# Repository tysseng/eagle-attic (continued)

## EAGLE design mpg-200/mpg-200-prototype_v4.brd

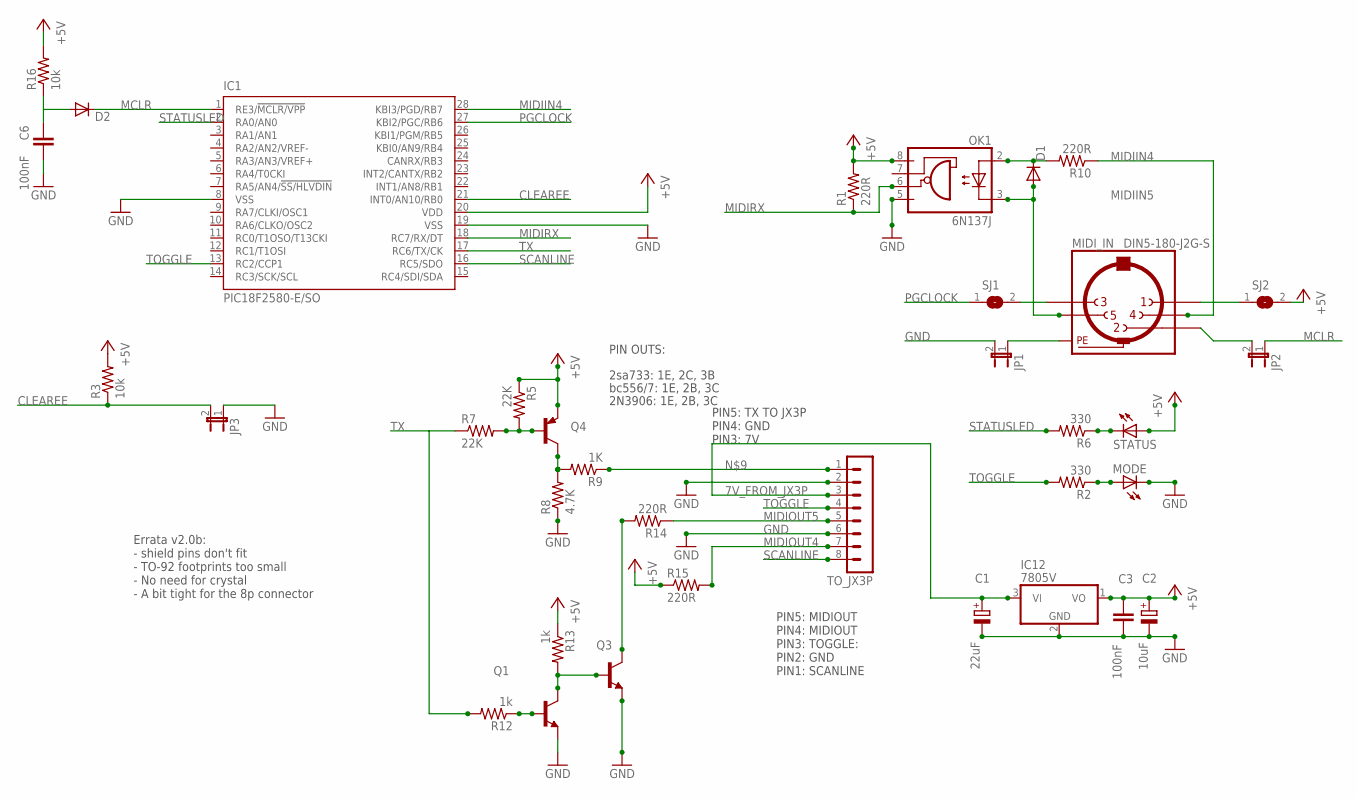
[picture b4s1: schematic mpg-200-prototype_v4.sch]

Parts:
C1: 22uF; E2,5-5
C2: 10uF; E2,5-5
C3, C6: 100nF; C0805
D1, D2: DIODE-SOD80C; SOD80C
IC1: PIC18F2580-E/SO; SO28W
IC12: 7805V; TO92
JP1, JP2, JP3: JP1E; JP1
MIDI_IN: DIN5-180-J2G-S; DIN5-180-J-DUAL-GND-SHORT
MODE: LED3MM
OK1: 6N137J; DIL08-J
Q1, Q3: 2N3904-NPN-TO92-EBC; TO92-EBC
Q4: 2N3906-PNP-TO92-EBC; TO92-EBC
R1, R10, R14, R15: 220R; R0805
R2, R6: 330; R0805
R3, R16: 10k; R0805
R5, R7: 22K; R0805
R8: 4.7K; R0805
R9: 1K; R0805
R12, R13: 1k; R0805
SJ1, SJ2: SJ
STATUS: LED3MM
TO_JX3P: MA08-1

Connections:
7V_FROM_JX3P: C1.+, IC12.3 (VI), TO_JX3P.3
+5V: C2.+, C3.1, IC1.20 (VDD), IC12.1 (VO), OK1.8 (VCC), Q4.E, R1.2, R3.2, R5.1, R13.1, R15.1, R16.2, SJ2.2, STATUS.A
CLEAREE: IC1.21 (INT0/AN10/RB0), JP3.2, R3.1
GND: C1.-, C2.-, C3.2, C6.2, IC1.8 (VSS), IC1.19 (VSS), IC12.2 (GND), JP1.2, JP3.1, MODE.K (C), OK1.5 (GND), Q1.E, Q3.E, R8.1, TO_JX3P.2, TO_JX3P.6
MCLR: D2.C, IC1.1 (RE3/!MCLR/VPP), JP2.1
MIDIIN4: IC1.28 (KBI3/PGD/RB7), MIDI_IN.4, R10.1
MIDIIN5: D1.A, MIDI_IN.5, OK1.3 (C)
MIDIOUT4: R15.2, TO_JX3P.7
MIDIOUT5: R14.1, TO_JX3P.5
MIDIRX: IC1.18 (RC7/RX/DT), OK1.6 (VO), R1.1
unnamed: R6.1, STATUS.K (C)
unnamed: Q4.B, R5.2, R7.2
unnamed: MODE.A, R2.1
unnamed: Q1.B, R12.1
unnamed: D1.C, OK1.2 (A), R10.2
unnamed: Q4.C, R8.2, R9.2
unnamed: Q1.C, Q3.B, R13.2
unnamed: Q3.C, R14.2
unnamed: R9.1, TO_JX3P.1
unnamed: MIDI_IN.3, SJ1.2
unnamed: JP2.2, MIDI_IN.2
unnamed: MIDI_IN.1, SJ2.1
unnamed: JP1.1, MIDI_IN.PE, MIDI_IN.PE@1 (PE), MIDI_IN.PE@2 (PE), MIDI_IN.PE@3 (PE)
unnamed: C6.1, D2.A, R16.1
PGCLOCK: IC1.27 (KBI2/PGC/RB6), SJ1.1
SCANLINE: IC1.16 (RC5/SDO), TO_JX3P.8
STATUSLED: IC1.2 (RA0/AN0), R6.2
TOGGLE: IC1.13 (RC2/CCP1), R2.2, TO_JX3P.4
TX: IC1.17 (RC6/TX/CK), R7.1, R12.2

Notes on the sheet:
2sa733: 1E, 2C, 3B
bc556/7: 1E, 2B, 3C
2N3906: 1E, 2B, 3C
PIN OUTS:
PIN5: MIDIOUT PIN4: MIDIOUT PIN3: TOGGLE: PIN2: GND PIN1: SCANLINE
PIN5: TX TO JX3P PIN4: GND PIN3: 7V
Errata v2.0b: - shield pins don't fit - TO-92 footprints too small - No need for crystal - A bit tight for the 8p connector

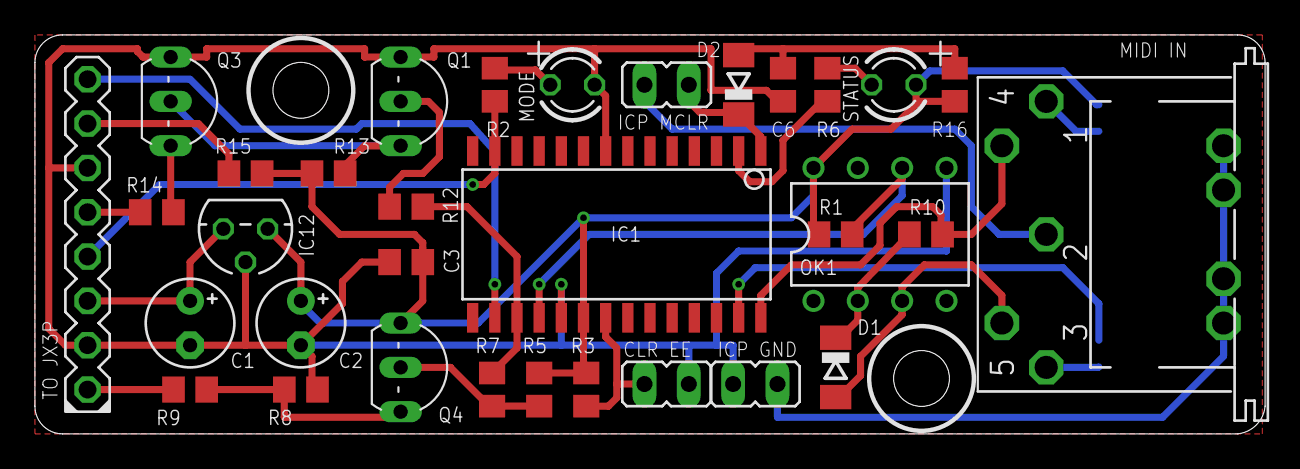
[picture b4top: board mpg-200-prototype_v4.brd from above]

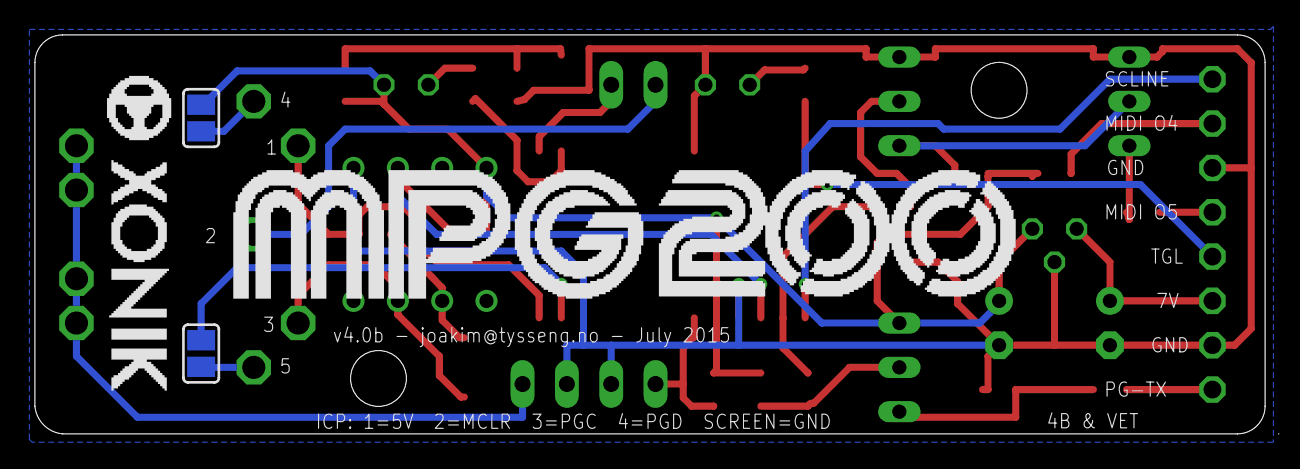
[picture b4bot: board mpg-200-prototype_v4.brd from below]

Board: 2 copper layers, 70.5 x 22.9 mm, 35 parts (2 on the bottom side), 29 nets.

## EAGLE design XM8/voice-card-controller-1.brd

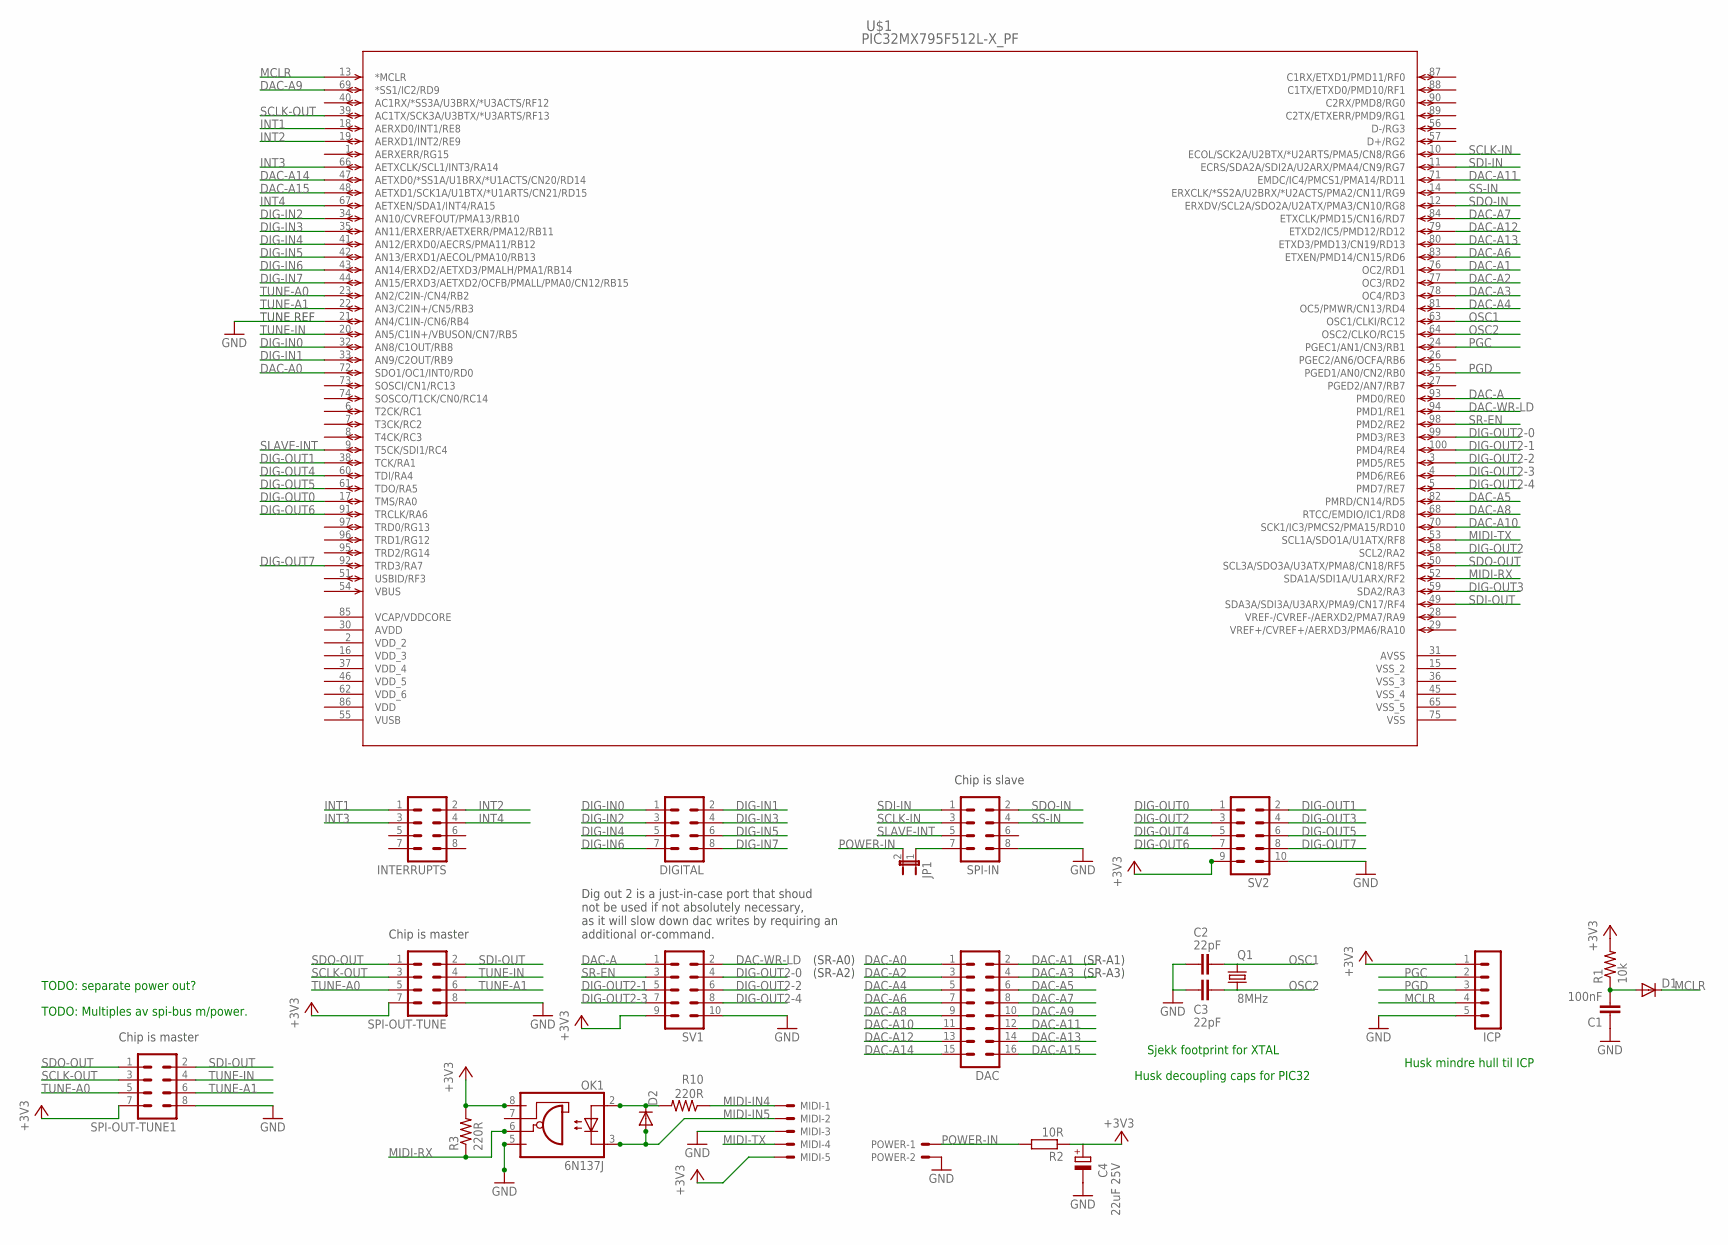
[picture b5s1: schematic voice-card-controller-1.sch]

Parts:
C1: 100nF; C0805
C2, C3: 22pF; C0805
C4: 22uF 25V; E2,5-5
D1, D2: DIODE-SOD80C; SOD80C
DAC: MA08-2
DIGITAL: MA04-2
ICP: MA05-1
INTERRUPTS: MA04-2
JP1: JP1E; JP1
MIDI: 22-23-2051
OK1: 6N137J; DIL08-J
POWER: 22-23-2021
Q1: 8MHz; SM49
R1: 10k; R0805
R2: 10R; 0207/7
R3, R10: 220R; R0805
SPI-IN: MA04-2
SPI-OUT-TUNE, SPI-OUT-TUNE1: MA04-2
SV1, SV2: MA05-2
U$1: PIC32MX795F512L-X_PF; TQFP100_14X14MC

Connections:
+3V3: C4.+, ICP.1, MIDI.5, OK1.8 (VCC), R1.2, R2.1, R3.2, SPI-OUT-TUNE.7, SPI-OUT-TUNE1.7, SV1.9, SV2.9
AVDD: U$1.30 (AVDD)
AVSS: U$1.31 (AVSS)
DAC-A: SV1.1, U$1.93 (PMD0/RE0)
DAC-A0: DAC.1, U$1.72 (SDO1/OC1/INT0/RD0)
DAC-A1: DAC.2, U$1.76 (OC2/RD1)
DAC-A2: DAC.3, U$1.77 (OC3/RD2)
DAC-A3: DAC.4, U$1.78 (OC4/RD3)
DAC-A4: DAC.5, U$1.81 (OC5/PMWR/CN13/RD4)
DAC-A5: DAC.6, U$1.82 (PMRD/CN14/RD5)
DAC-A6: DAC.7, U$1.83 (ETXEN/PMD14/CN15/RD6)
DAC-A7: DAC.8, U$1.84 (ETXCLK/PMD15/CN16/RD7)
DAC-A8: DAC.9, U$1.68 (RTCC/EMDIO/IC1/RD8)
DAC-A9: DAC.10, U$1.69 (*SS1/IC2/RD9)
DAC-A10: DAC.11, U$1.70 (SCK1/IC3/PMCS2/PMA15/RD10)
DAC-A11: DAC.12, U$1.71 (EMDC/IC4/PMCS1/PMA14/RD11)
DAC-A12: DAC.13, U$1.79 (ETXD2/IC5/PMD12/RD12)
DAC-A13: DAC.14, U$1.80 (ETXD3/PMD13/CN19/RD13)
DAC-A14: DAC.15, U$1.47 (AETXD0/*SS1A/U1BRX/*U1ACTS/CN20/RD14)
DAC-A15: DAC.16, U$1.48 (AETXD1/SCK1A/U1BTX/*U1ARTS/CN21/RD15)
DAC-WR-LD: SV1.2, U$1.94 (PMD1/RE1)
DIG-IN0: DIGITAL.1, U$1.32 (AN8/C1OUT/RB8)
DIG-IN1: DIGITAL.2, U$1.33 (AN9/C2OUT/RB9)
DIG-IN2: DIGITAL.3, U$1.34 (AN10/CVREFOUT/PMA13/RB10)
DIG-IN3: DIGITAL.4, U$1.35 (AN11/ERXERR/AETXERR/PMA12/RB11)
DIG-IN4: DIGITAL.5, U$1.41 (AN12/ERXD0/AECRS/PMA11/RB12)
DIG-IN5: DIGITAL.6, U$1.42 (AN13/ERXD1/AECOL/PMA10/RB13)
DIG-IN6: DIGITAL.7, U$1.43 (AN14/ERXD2/AETXD3/PMALH/PMA1/RB14)
DIG-IN7: DIGITAL.8, U$1.44 (AN15/ERXD3/AETXD2/OCFB/PMALL/PMA0/CN12/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)
DIG-OUT0: SV2.1, U$1.17 (TMS/RA0)
DIG-OUT1: SV2.2, U$1.38 (TCK/RA1)
DIG-OUT2: SV2.3, U$1.58 (SCL2/RA2)
DIG-OUT2-0: SV1.4, U$1.99 (PMD3/RE3)
DIG-OUT2-1: SV1.5, U$1.100 (PMD4/RE4)
DIG-OUT2-2: SV1.6, U$1.3 (PMD5/RE5)
DIG-OUT2-3: SV1.7, U$1.4 (PMD6/RE6)
DIG-OUT2-4: SV1.8, U$1.5 (PMD7/RE7)
DIG-OUT3: SV2.4, U$1.59 (SDA2/RA3)
DIG-OUT4: SV2.5, U$1.60 (TDI/RA4)
DIG-OUT5: SV2.6, U$1.61 (TDO/RA5)
DIG-OUT6: SV2.7, U$1.91 (TRCLK/RA6)
DIG-OUT7: SV2.8, U$1.92 (TRD3/RA7)
GND: C1.1, C2.2, C3.2, C4.-, ICP.5, MIDI.3, OK1.5 (GND), POWER.2, SPI-IN.8, SPI-OUT-TUNE.8, SPI-OUT-TUNE1.8, SV1.10, SV2.10, U$1.21 (AN4/C1IN-/CN6/RB4)
INT1: INTERRUPTS.1, U$1.18 (AERXD0/INT1/RE8)
INT2: INTERRUPTS.2, U$1.19 (AERXD1/INT2/RE9)
INT3: INTERRUPTS.3, U$1.66 (AETXCLK/SCL1/INT3/RA14)
INT4: INTERRUPTS.4, U$1.67 (AETXEN/SDA1/INT4/RA15)
MCLR: D1.C, ICP.4, U$1.13 (*MCLR)
MIDI-IN4: MIDI.1, R10.1
MIDI-IN5: D2.A, MIDI.2, OK1.3 (C)
MIDI-RX: OK1.6 (VO), R3.1, U$1.52 (SDA1A/SDI1A/U1ARX/RF2)
MIDI-TX: MIDI.4, U$1.53 (SCL1A/SDO1A/U1ATX/RF8)
unnamed: JP1.1, SPI-IN.7
unnamed: C1.2, D1.A, R1.1
unnamed: D2.C, OK1.2 (A), R10.2
OSC1: C2.1, Q1.2, U$1.63 (OSC1/CLKI/RC12)
OSC2: C3.1, Q1.1, U$1.64 (OSC2/CLKO/RC15)
PGC: ICP.2, U$1.24 (PGEC1/AN1/CN3/RB1)
PGD: ICP.3, U$1.25 (PGED1/AN0/CN2/RB0)
POWER-IN: JP1.2, POWER.1, R2.2
SCLK-IN: SPI-IN.3, U$1.10 (ECOL/SCK2A/U2BTX/*U2ARTS/PMA5/CN8/RG6)
SCLK-OUT: SPI-OUT-TUNE.3, SPI-OUT-TUNE1.3, U$1.39 (AC1TX/SCK3A/U3BTX/*U3ARTS/RF13)
SDI-IN: SPI-IN.1, U$1.11 (ECRS/SDA2A/SDI2A/U2ARX/PMA4/CN9/RG7)
SDI-OUT: SPI-OUT-TUNE.2, SPI-OUT-TUNE1.2, U$1.49 (SDA3A/SDI3A/U3ARX/PMA9/CN17/RF4)
SDO-IN: SPI-IN.2, U$1.12 (ERXDV/SCL2A/SDO2A/U2ATX/PMA3/CN10/RG8)
SDO-OUT: SPI-OUT-TUNE.1, SPI-OUT-TUNE1.1, U$1.50 (SCL3A/SDO3A/U3ATX/PMA8/CN18/RF5)
SLAVE-INT: SPI-IN.5, U$1.9 (T5CK/SDI1/RC4)
SR-EN: SV1.3, U$1.98 (PMD2/RE2)
SS-IN: SPI-IN.4, U$1.14 (ERXCLK/*SS2A/U2BRX/*U2ACTS/PMA2/CN11/RG9)
TUNE-A0: SPI-OUT-TUNE.5, SPI-OUT-TUNE1.5, U$1.23 (AN2/C2IN-/CN4/RB2)
TUNE-A1: SPI-OUT-TUNE.6, SPI-OUT-TUNE1.6, U$1.22 (AN3/C2IN+/CN5/RB3)
TUNE-IN: SPI-OUT-TUNE.4, SPI-OUT-TUNE1.4, U$1.20 (AN5/C1IN+/VBUSON/CN7/RB5)
VCAP/VDDCORE: U$1.85 (VCAP/VDDCORE)
VDD: U$1.86 (VDD)
VDD_2: U$1.2 (VDD_2)
VDD_3: U$1.16 (VDD_3)
VDD_4: U$1.37 (VDD_4)
VDD_5: U$1.46 (VDD_5)
VDD_6: U$1.62 (VDD_6)
VSS: U$1.75 (VSS)
VSS_2: U$1.15 (VSS_2)
VSS_3: U$1.36 (VSS_3)
VSS_4: U$1.45 (VSS_4)
VSS_5: U$1.65 (VSS_5)
VUSB: U$1.55 (VUSB)

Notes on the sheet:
Husk mindre hull til ICP
Husk decoupling caps for PIC32
Sjekk footprint for XTAL
(SR-A0)
(SR-A2)
(SR-A1)
(SR-A3)
Chip is slave
Chip is master
TUNE REF
Dig out 2 is a just-in-case port that shoud not be used if not absolutely necessary, as it will slow down dac writes by requiring an additional or-command.
TODO: Multiples av spi-bus m/power.
TODO: separate power out?

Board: 2 copper layers, 25 parts (0 on the bottom side), 70 nets, no tracks yet.

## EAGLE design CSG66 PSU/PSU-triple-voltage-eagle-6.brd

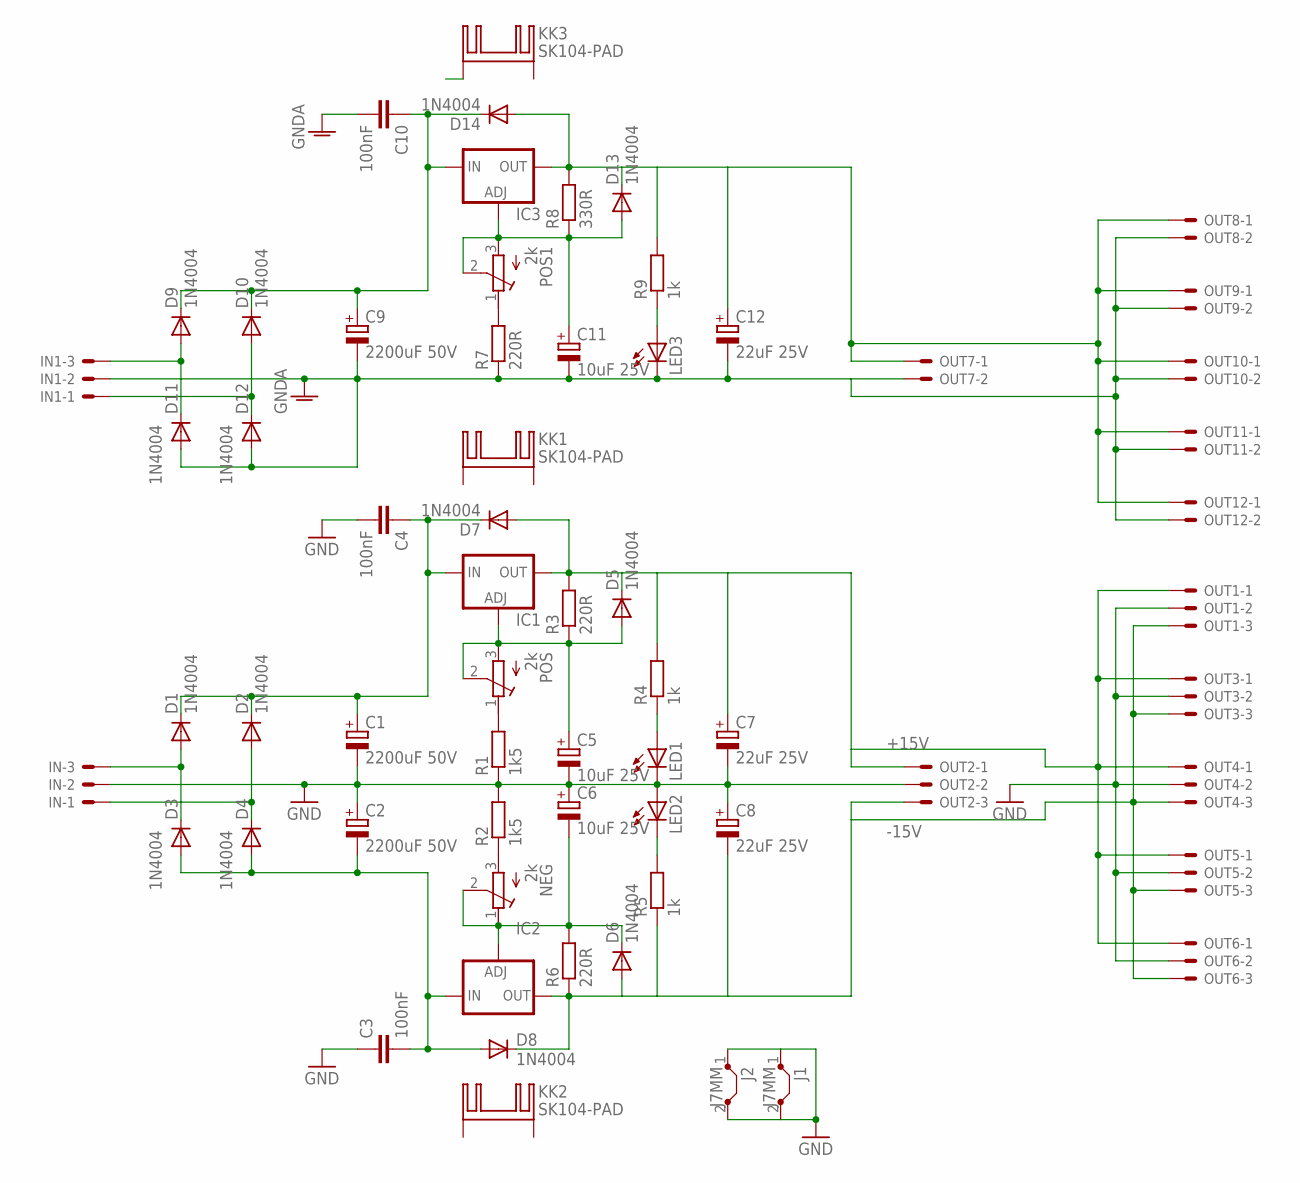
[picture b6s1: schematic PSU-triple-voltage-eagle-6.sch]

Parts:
C1, C2, C9: 2200uF 50V; E7,5-16
C3, C4, C10: 100nF; C050-025X075
C5, C6, C11: 10uF 25V; E2,5-5
C7, C8, C12: 22uF 25V; E2,5-5
D1, D2, D3, D4, D5, D6, D7, D8, D9, D10, D11, D12, D13, D14: 1N4004; DO41-10
IC1, IC3: LM317TS; 317TS
IC2: LM337TS; 337TS
IN, IN1: KK-156-3
J1, J2: J7MM; 07
KK1, KK2, KK3: SK104-PAD
LED1, LED2, LED3: LED3MM
NEG: 2k; RTRIMT93YA
OUT1, OUT2, OUT3, OUT4, OUT5, OUT6: KK-156-3
OUT7, OUT8, OUT9, OUT10, OUT11, OUT12: KK-156-2
POS, POS1: 2k; RTRIMT93YA
R1, R2: 1k5; 0207/7
R3, R6, R7: 220R; 0207/7
R4, R5, R9: 1k; 0207/7
R8: 330R; 0207/7

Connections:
+5V: C12.+, D13.C, D14.A, IC3.2 (OUT), OUT7.1, OUT8.1, OUT9.1, OUT10.1, OUT11.1, OUT12.1, R8.2, R9.2
+15V: C7.+, D5.C, D7.A, IC1.2 (OUT), OUT1.1, OUT2.1, OUT3.1, OUT4.1, OUT5.1, OUT6.1, R3.2, R4.2
-15V: C8.-, D6.A, D8.C, IC2.3 (OUT), OUT1.3, OUT2.3, OUT3.3, OUT4.3, OUT5.3, OUT6.3, R5.1, R6.1
GND: C1.-, C2.+, C3.1, C4.2, C5.-, C6.+, C7.-, C8.+, IN.2, J1.1, J1.2, J2.1, J2.2, LED1.K (C), LED2.A, OUT1.2, OUT2.2, OUT3.2, OUT4.2, OUT5.2, OUT6.2, R1.1, R2.2
GNDA: C9.-, C10.2, C11.-, C12.-, D11.A, D12.A, IN1.2, LED3.K (C), OUT7.2, OUT8.2, OUT9.2, OUT10.2, OUT11.2, OUT12.2, R7.1
unnamed: LED3.A, R9.1
unnamed: POS1.1 (E), R7.2
unnamed: C11.+, D13.A, IC3.1 (ADJ), POS1.2 (S), POS1.3 (A), R8.1
unnamed: LED1.A, R4.1
unnamed: C9.+, C10.1, D9.C, D10.C, D14.C, IC3.3 (IN)
unnamed: LED2.K (C), R5.2
unnamed: D10.A, D12.C, IN1.1
unnamed: POS.1 (E), R1.2
unnamed: C5.+, D5.A, IC1.1 (ADJ), POS.2 (S), POS.3 (A), R3.1
unnamed: NEG.3 (A), R2.1
unnamed: C6.-, D6.C, IC2.1 (ADJ), NEG.1 (E), NEG.2 (S), R6.2
unnamed: C2.-, C3.2, D3.A, D4.A, D8.A, IC2.2 (IN)
unnamed: D9.A, D11.C, IN1.3
unnamed: C1.+, C4.1, D1.C, D2.C, D7.C, IC1.3 (IN)
unnamed: D2.A, D4.C, IN.1
unnamed: D1.A, D3.C, IN.3

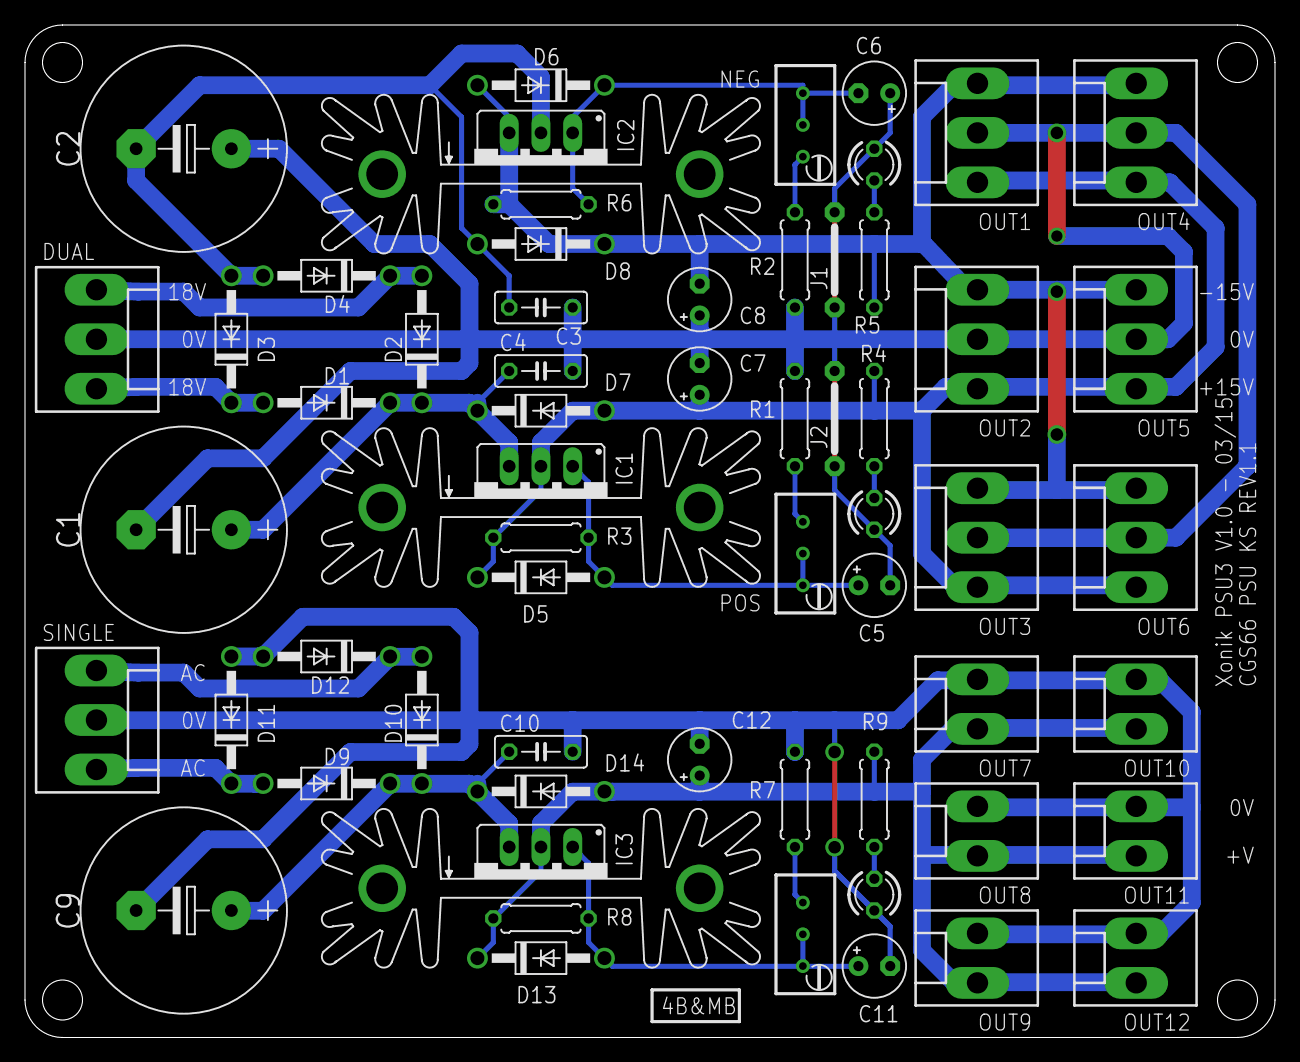
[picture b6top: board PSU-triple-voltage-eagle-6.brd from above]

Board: 2 copper layers, 100.0 x 81.0 mm, 63 parts (0 on the bottom side), 21 nets.

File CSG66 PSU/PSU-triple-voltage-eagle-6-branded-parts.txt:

Partlist

Exported from PSU-triple-voltage-eagle-6-branded.sch at 01.03.2015 13:05:13

EAGLE Version 6.2.0 Copyright (c) 1988-2012 CadSoft

Assembly variant: 

Part     Value          Device          Package      Library   Sheet

C1       2200uF 50V     CPOL-EUE7.5-16  E7,5-16      resistor  1
C2       2200uF 50V     CPOL-EUE7.5-16  E7,5-16      resistor  1
C3       100nF          C-EU050-025X075 C050-025X075 resistor  1
C4       100nF          C-EU050-025X075 C050-025X075 resistor  1
C5       10uF 25V       CPOL-EUE2.5-5   E2,5-5       resistor  1
C6       10uF 25V       CPOL-EUE2.5-5   E2,5-5       resistor  1
C7       22uF 25V       CPOL-EUE2.5-5   E2,5-5       resistor  1
C8       22uF 25V       CPOL-EUE2.5-5   E2,5-5       resistor  1
C9       2200uF 50V     CPOL-EUE7.5-16  E7,5-16      resistor  1
C10      100nF          C-EU050-025X075 C050-025X075 resistor  1
C11      10uF 25V       CPOL-EUE2.5-5   E2,5-5       resistor  1
C12      22uF 25V       CPOL-EUE2.5-5   E2,5-5       resistor  1
D1       1N4004         1N4004          DO41-10      diode     1
D2       1N4004         1N4004          DO41-10      diode     1
D3       1N4004         1N4004          DO41-10      diode     1
D4       1N4004         1N4004          DO41-10      diode     1
D5       1N4004         1N4004          DO41-10      diode     1
D6       1N4004         1N4004          DO41-10      diode     1
D7       1N4004         1N4004          DO41-10      diode     1
D8       1N4004         1N4004          DO41-10      diode     1
D9       1N4004         1N4004          DO41-10      diode     1
D10      1N4004         1N4004          DO41-10      diode     1
D11      1N4004         1N4004          DO41-10      diode     1
D12      1N4004         1N4004          DO41-10      diode     1
D13      1N4004         1N4004          DO41-10      diode     1
D14      1N4004         1N4004          DO41-10      diode     1
IC1                     LM317TS         317TS        v-reg     1
IC2                     LM337TS         337TS        v-reg     1
IC3                     LM317TS         317TS        v-reg     1
IN                      KK-156-3        KK-156-3     con-molex 1
IN1                     KK-156-3        KK-156-3     con-molex 1
KK1      SK104-PAD      SK104-PAD       SK104-PAD    heatsink  1
KK2      SK104-PAD      SK104-PAD       SK104-PAD    heatsink  1
KK3      SK104-PAD      SK104-PAD       SK104-PAD    heatsink  1
LED1                    LED3MM          LED3MM       led       1
LED2                    LED3MM          LED3MM       led       1
LED3                    LED3MM          LED3MM       led       1
NEG      2k             R-TRIMMT93YA    RTRIMT93YA   resistor  1
OUT1                    KK-156-3        KK-156-3     con-molex 1
OUT2                    KK-156-3        KK-156-3     con-molex 1
OUT3                    KK-156-3        KK-156-3     con-molex 1
OUT4                    KK-156-3        KK-156-3     con-molex 1
OUT5                    KK-156-3        KK-156-3     con-molex 1
OUT6                    KK-156-3        KK-156-3     con-molex 1
OUT7                    KK-156-2        KK-156-2     con-molex 1
OUT8                    KK-156-2        KK-156-2     con-molex 1
OUT9                    KK-156-2        KK-156-2     con-molex 1
OUT10                   KK-156-2        KK-156-2     con-molex 1
OUT11                   KK-156-2        KK-156-2     con-molex 1
OUT12                   KK-156-2        KK-156-2     con-molex 1
POS      2k             R-TRIMMT93YA    RTRIMT93YA   resistor  1
POS1     2k             R-TRIMMT93YA    RTRIMT93YA   resistor  1
R1       1k5            R-EU_0207/7     0207/7       resistor  1
R2       1k5            R-EU_0207/7     0207/7       resistor  1
R3       220R           R-EU_0207/7     0207/7       resistor  1
R4       1k             R-EU_0207/7     0207/7       resistor  1
R5       1k             R-EU_0207/7     0207/7       resistor  1
R6       220R           R-EU_0207/7     0207/7       resistor  1
R7       220R           R-EU_0207/7     0207/7       resistor  1
R8       330R           R-EU_0207/7     0207/7       resistor  1
R9       1k             R-EU_0207/7     0207/7       resistor  1

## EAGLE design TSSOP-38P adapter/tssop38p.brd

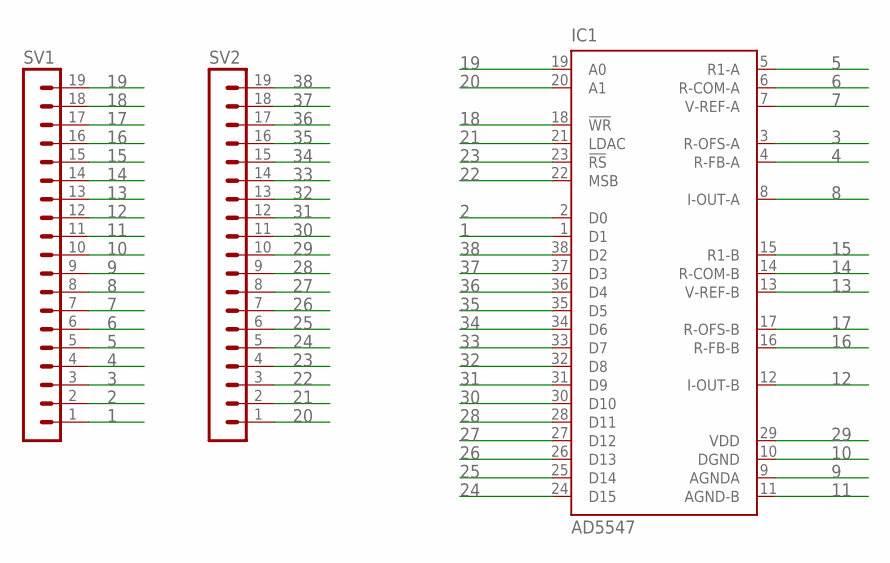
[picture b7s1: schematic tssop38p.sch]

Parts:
IC1: AD5547; TSSOP38
SV1, SV2: MA19-1J

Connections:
1: IC1.1 (D1), SV1.1
2: IC1.2 (D0), SV1.2
3: IC1.3 (R-OFS-A), SV1.3
4: IC1.4 (R-FB-A), SV1.4
5: IC1.5 (R1-A), SV1.5
6: IC1.6 (R-COM-A), SV1.6
7: IC1.7 (V-REF-A), SV1.7
8: IC1.8 (I-OUT-A), SV1.8
9: IC1.9 (AGNDA), SV1.9
10: IC1.10 (DGND), SV1.10
11: IC1.11 (AGND-B), SV1.11
12: IC1.12 (I-OUT-B), SV1.12
13: IC1.13 (V-REF-B), SV1.13
14: IC1.14 (R-COM-B), SV1.14
15: IC1.15 (R1-B), SV1.15
16: IC1.16 (R-FB-B), SV1.16
17: IC1.17 (R-OFS-B), SV1.17
18: IC1.18 (!WR), SV1.18
19: IC1.19 (A0), SV1.19
20: IC1.20 (A1), SV2.1
21: IC1.21 (LDAC), SV2.2
22: IC1.22 (MSB), SV2.3
23: IC1.23 (!RS), SV2.4
24: IC1.24 (D15), SV2.5
25: IC1.25 (D14), SV2.6
26: IC1.26 (D13), SV2.7
27: IC1.27 (D12), SV2.8
28: IC1.28 (D11), SV2.9
29: IC1.29 (VDD), SV2.10
30: IC1.30 (D10), SV2.11
31: IC1.31 (D9), SV2.12
32: IC1.32 (D8), SV2.13
33: IC1.33 (D7), SV2.14
34: IC1.34 (D6), SV2.15
35: IC1.35 (D5), SV2.16
36: IC1.36 (D4), SV2.17
37: IC1.37 (D3), SV2.18
38: IC1.38 (D2), SV2.19

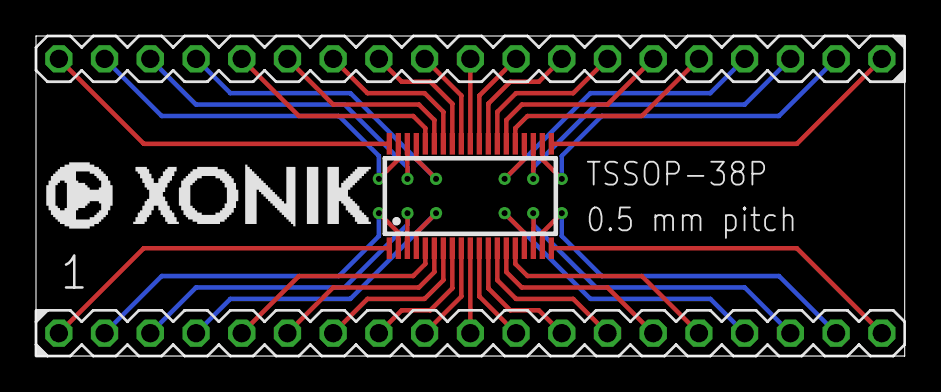
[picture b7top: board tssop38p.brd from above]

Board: 2 copper layers, 48.3 x 17.8 mm, 3 parts (0 on the bottom side), 38 nets.

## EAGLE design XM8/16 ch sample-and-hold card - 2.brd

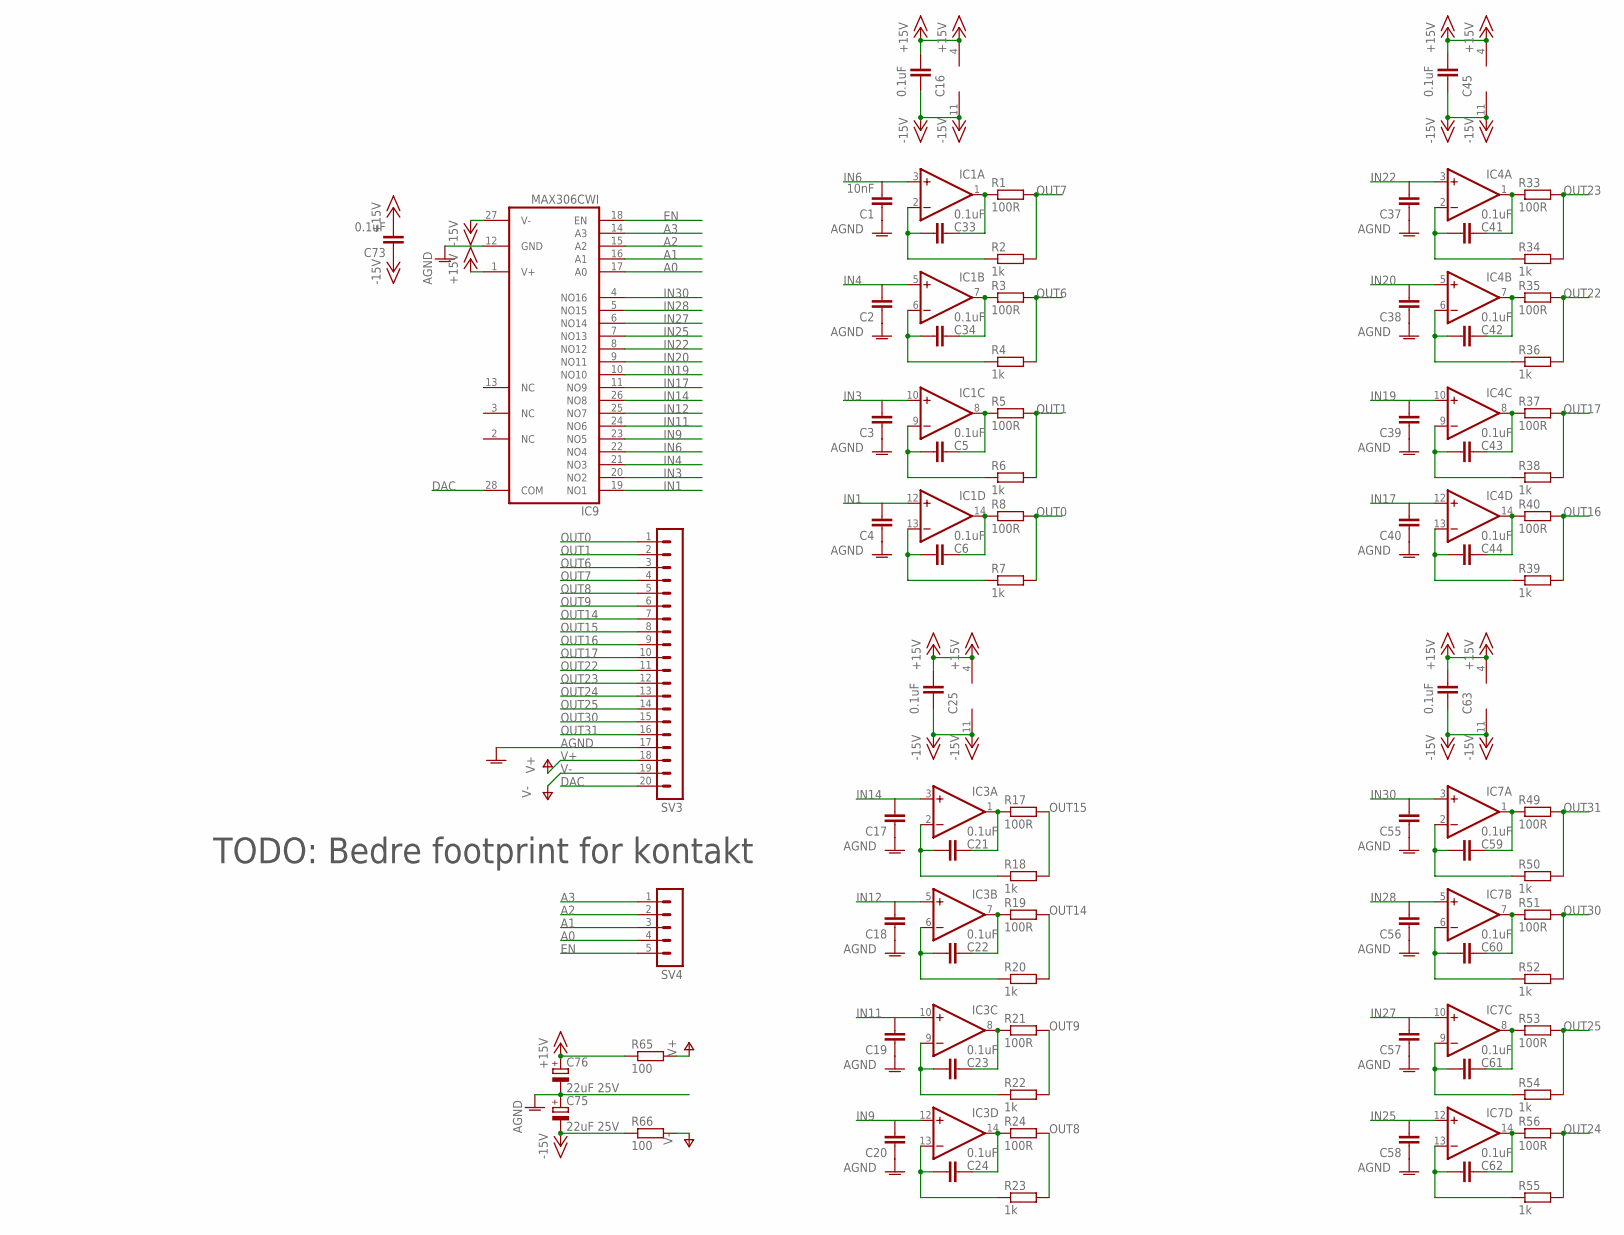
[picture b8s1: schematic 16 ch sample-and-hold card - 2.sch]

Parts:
C1: 10nF; C1206
C2, C3, C4, C17, C18, C19, C20, C37, C38, C39, C40, C55, C56, C57, C58: C-EUC1206; C1206
C5, C6, C16, C21, C22, C23, C24, C25, C33, C34, C41, C42, C43, C44, C45, C59, C60, C61, C62, C63, C73: 0.1uF; C0603
C75, C76: 22uF 25V; E2-5
IC1, IC3, IC4, IC7: TL074D; SO14
IC9: MAX306CWI; SO28L
R1, R3, R5, R8, R17, R19, R21, R24, R33, R35, R37, R40, R49, R51, R53, R56: 100R; R0603
R2, R4, R6, R7, R18, R20, R22, R23, R34, R36, R38, R39, R50, R52, R54, R55: 1k; R0603
R65, R66: 100; 0207/7
SV3: MA20-1
SV4: MA05-1

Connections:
+15V: C16.1, C25.1, C45.1, C63.1, C73.2, C76.+, IC1.4 (V+), IC3.4 (V+), IC4.4 (V+), IC7.4 (V+), IC9.1 (V+), R65.1
-15V: C16.2, C25.2, C45.2, C63.2, C73.1, C75.-, IC1.11 (V-), IC3.11 (V-), IC4.11 (V-), IC7.11 (V-), IC9.27 (V-), R66.1
A0: IC9.17 (A0), SV4.4
A1: IC9.16 (A1), SV4.3
A2: IC9.15 (A2), SV4.2
A3: IC9.14 (A3), SV4.1
AGND: C1.1, C2.1, C3.1, C4.1, C17.1, C18.1, C19.1, C20.1, C37.1, C38.1, C39.1, C40.1, C55.1, C56.1, C57.1, C58.1, C75.+, C76.-, IC9.12 (GND), SV3.17
DAC: IC9.28 (COM), SV3.20
EN: IC9.18 (EN), SV4.5
IN1: C4.2, IC1.12 (+IN), IC9.19 (NO1)
IN3: C3.2, IC1.10 (+IN), IC9.20 (NO2)
IN4: C2.2, IC1.5 (+IN), IC9.21 (NO3)
IN6: C1.2, IC1.3 (+IN), IC9.22 (NO4)
IN9: C20.2, IC3.12 (+IN), IC9.23 (NO5)
IN11: C19.2, IC3.10 (+IN), IC9.24 (NO6)
IN12: C18.2, IC3.5 (+IN), IC9.25 (NO7)
IN14: C17.2, IC3.3 (+IN), IC9.26 (NO8)
IN17: C40.2, IC4.12 (+IN), IC9.11 (NO9)
IN19: C39.2, IC4.10 (+IN), IC9.10 (NO10)
IN20: C38.2, IC4.5 (+IN), IC9.9 (NO11)
IN22: C37.2, IC4.3 (+IN), IC9.8 (NO12)
IN25: C58.2, IC7.12 (+IN), IC9.7 (NO13)
IN27: C57.2, IC7.10 (+IN), IC9.6 (NO14)
IN28: C56.2, IC7.5 (+IN), IC9.5 (NO15)
IN30: C55.2, IC7.3 (+IN), IC9.4 (NO16)
unnamed: C33.2, IC1.2 (-IN), R2.1
unnamed: C33.1, IC1.1 (OUT), R1.1
unnamed: C34.1, IC1.7 (OUT), R3.1
unnamed: C5.1, IC1.8 (OUT), R5.1
unnamed: C34.2, IC1.6 (-IN), R4.1
unnamed: C6.1, IC1.14 (OUT), R8.1
unnamed: C5.2, IC1.9 (-IN), R6.1
unnamed: C6.2, IC1.13 (-IN), R7.1
unnamed: C21.1, IC3.1 (OUT), R17.1
unnamed: C21.2, IC3.2 (-IN), R18.1
unnamed: C22.1, IC3.7 (OUT), R19.1
unnamed: C22.2, IC3.6 (-IN), R20.1
unnamed: C23.1, IC3.8 (OUT), R21.1
unnamed: C24.1, IC3.14 (OUT), R24.1
unnamed: C23.2, IC3.9 (-IN), R22.1
unnamed: C24.2, IC3.13 (-IN), R23.1
unnamed: C41.1, IC4.1 (OUT), R33.1
unnamed: C41.2, IC4.2 (-IN), R34.1
unnamed: C42.1, IC4.7 (OUT), R35.1
unnamed: C42.2, IC4.6 (-IN), R36.1
unnamed: C43.1, IC4.8 (OUT), R37.1
unnamed: C44.1, IC4.14 (OUT), R40.1
unnamed: C43.2, IC4.9 (-IN), R38.1
unnamed: C44.2, IC4.13 (-IN), R39.1
unnamed: C59.1, IC7.1 (OUT), R49.1
unnamed: C59.2, IC7.2 (-IN), R50.1
unnamed: C60.1, IC7.7 (OUT), R51.1
unnamed: C60.2, IC7.6 (-IN), R52.1
unnamed: C61.1, IC7.8 (OUT), R53.1
unnamed: C62.1, IC7.14 (OUT), R56.1
unnamed: C61.2, IC7.9 (-IN), R54.1
unnamed: C62.2, IC7.13 (-IN), R55.1
OUT0: R7.2, R8.2, SV3.1
OUT1: R5.2, R6.2, SV3.2
OUT6: R3.2, R4.2, SV3.3
OUT7: R1.2, R2.2, SV3.4
OUT8: R23.2, R24.2, SV3.5
OUT9: R21.2, R22.2, SV3.6
OUT14: R19.2, R20.2, SV3.7
OUT15: R17.2, R18.2, SV3.8
OUT16: R39.2, R40.2, SV3.9
OUT17: R37.2, R38.2, SV3.10
OUT22: R35.2, R36.2, SV3.11
OUT23: R33.2, R34.2, SV3.12
OUT24: R55.2, R56.2, SV3.13
OUT25: R53.2, R54.2, SV3.14
OUT30: R51.2, R52.2, SV3.15
OUT31: R49.2, R50.2, SV3.16
V+: R65.2, SV3.18
V-: R66.2, SV3.19

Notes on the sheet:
TODO: Bedre footprint for kontakt

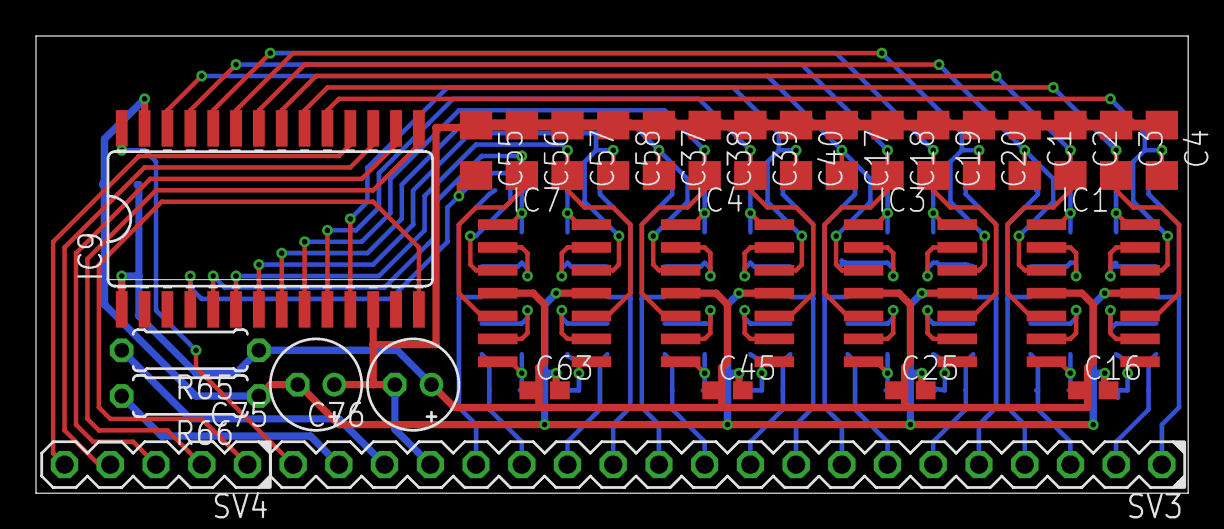
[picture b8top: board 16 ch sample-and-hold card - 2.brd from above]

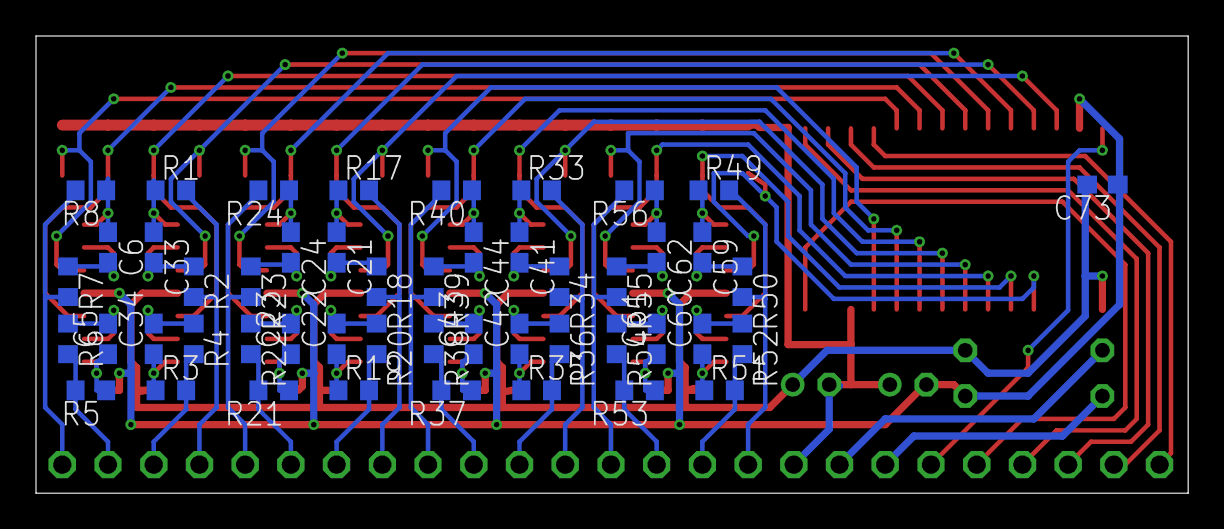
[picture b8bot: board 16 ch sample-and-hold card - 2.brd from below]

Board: 2 copper layers, 64.0 x 25.4 mm, 80 parts (49 on the bottom side), 75 nets.

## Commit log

2017-09-08 Initial commit, moved contents from google drive
2018-01-27 updated 7-saw
2018-01-27 Moved to xonik
2018-01-27 duplicate with Machinebeats
